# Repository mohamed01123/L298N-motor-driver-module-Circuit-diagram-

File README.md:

📁 L298N Motor Driver Module – Custom Circuit Design
📌 Overview
This project involves designing a custom motor driver circuit based on the L298N dual H-Bridge IC. The goal is to control two DC motors through a microcontroller with added protection and regulated power supply. The circuit supports external power input and can safely interface with most microcontrollers (e.g., ATmega32, Arduino, STM32).

🧩 Components Used
Component                	Quantity  	Description
L298N Motor Driver IC        	1     	Dual full-bridge driver for controlling two DC motors
7805 Voltage Regulator	      1      	Provides regulated 5V from external power supply
1N4007 Diodes (or similar)	  8	      Flyback diodes to protect the L298N from motor back-EMF
LED                          	1	      Power status indicator
Resistor (330Ω–1kΩ)	          1	      Current limiting resistor for the LED
3-Pin Screw Terminal	        1      	For external power input: GND, +5V, VCC (motor power)
2-Pin Screw Terminals       	2      	For connecting two DC motors (Motor A and Motor B)
6-Pin Socket Header         	1     	Interface with microcontroller (ENA, IN1, IN2, IN3, IN4, ENB)
2-Pin Jumper Socket          	1     	To optionally bridge +5V logic and +5V motor power (for shared supply

⚙️ Circuit Description

 🔌 Power Supply Section
A 3-pin screw terminal is used to connect:
GND
+5V (Logic supply) – Can come from the microcontroller or regulated 5V from 7805
VCC (Motor supply) – Power input for the motors, typically 6V to 12V
The 7805 voltage regulator steps down motor power (VCC) to a clean 5V for logic use.
A 2-pin jumper socket is used to optionally connect the 5V from the 7805 to the logic supply, allowing shared or isolated supplies.

🚦 Indicator LED
An LED with a current-limiting resistor is connected across the regulated 5V and GND to indicate power status.

🧠 L298N Control Logic
The L298N IC takes six control inputs:
ENA – Enable Motor A
IN1, IN2 – Direction control for Motor A
IN3, IN4 – Direction control for Motor B
ENB – Enable Motor B
A 6-pin female header socket is used to connect these control lines to a microcontroller.

🔄 Motor Connections
Two 2-pin screw terminals are used to connect Motor A and Motor B to the output of the L298N.

🛡️ Protection Diodes
8 diodes are placed across the motor output pins (OUT1–OUT4) and power supply lines to safeguard the L298N IC from inductive spikes and magnetic back-EMF generated by the motors.
🔗 Microcontroller Interface
Pin on Socket	        Function
ENA                 	Enable Motor A (PWM capable pin)
IN1	                  Motor A Direction 1
IN2                  	Motor A Direction 2
IN3                 	Motor B Direction 1
IN4                 	Motor B Direction 2
ENB	                  Enable Motor B (PWM capable pin)
Use the ENA/ENB pins with PWM output from your microcontroller to control motor speed.

📝 Notes
Keep heatsink on L298  if using motors with higher current demand.
Always check the power rating of your motors and match the VCC input accordingly.
When using only one power supply, close the jumper to connect 5V logic with the output from 7805.
If using separate supplies for logic and motors, keep the jumper open and make sure both share a common ground.

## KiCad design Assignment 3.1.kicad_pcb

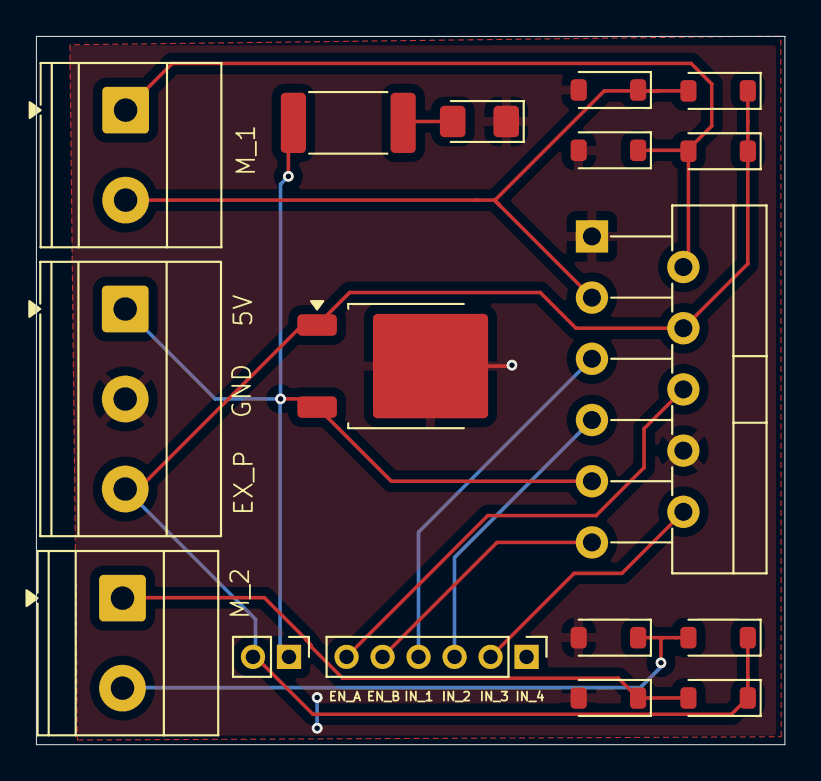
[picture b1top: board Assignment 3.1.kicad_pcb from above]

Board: 2 copper layers, 41.6 x 39.3 mm, 17 parts (0 on the bottom side), 13 nets.

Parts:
D1, D3, D4, D5, D6, D7, D8, D9: BAV16W; D_SOD-123
D2: LED; LED_1206_3216Metric_Pad1.42x1.75mm_HandSolder
J1, J4: Conn_01x02_Pin; TerminalBlock_Phoenix_MKDS-1,5-2_1x02_P5.00mm_Horizontal
J2: Conn_01x03_Pin; TerminalBlock_Phoenix_MKDS-1,5-3_1x03_P5.00mm_Horizontal
J3: Conn_01x06_Pin; PinHeader_1x06_P2.00mm_Vertical
J5: Conn_01x02_Pin S; PinHeader_1x02_P2.00mm_Vertical
R1: 330; R_2512_6332Metric_Pad1.40x3.35mm_HandSolder
U1: L298HN; TO-220-11_P3.4x5.08mm_StaggerOdd_Lead4.58mm_Vertical
U2: L7805; TO-252-2

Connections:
5V: J2.1, J5.1, R1.2, U1.9 (Vss), U2.3 (OUT)
EN_A: J3.6, U1.6 (EnA)
EN_B: J3.5, U1.11 (EnB)
EX_Power: D1.1 (K), D3.1 (K), D4.1 (K), D5.1 (K), J2.3, J5.2, U1.4 (Vs), U2.1 (IN)
GND: D2.1 (K), D6.2 (A), D7.2 (A), D8.2 (A), D9.2 (A), J2.2, U1.1 (SENSE_A), U1.8 (GND), U2.2 (GND)
IN_1: J3.4, U1.5 (IN1)
IN_2: J3.3, U1.7 (IN2)
IN_3: J3.2, U1.10 (IN3)
unnamed: D2.2 (A), R1.1
OUT_1: D1.2 (A), D6.1 (K), J1.1, U1.2 (OUT1)
OUT_2: D3.2 (A), D7.1 (K), J1.2, U1.3 (OUT2)
OUT_3: D4.2 (A), D8.1 (K), J4.1
OUT_4: D5.2 (A), D9.1 (K), J4.2

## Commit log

2025-05-26 The frist commit
